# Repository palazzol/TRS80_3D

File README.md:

# TRS80_3D

## Stereo 3D graphics on a TRS-80 Model III

#### To be seen at [Tandy Assembly 2022](http://www.tandyassembly.com/)

## RAMBO board - 1 Meg "RAMDisk"

## Simulated Video - click to animate (YouTube link)

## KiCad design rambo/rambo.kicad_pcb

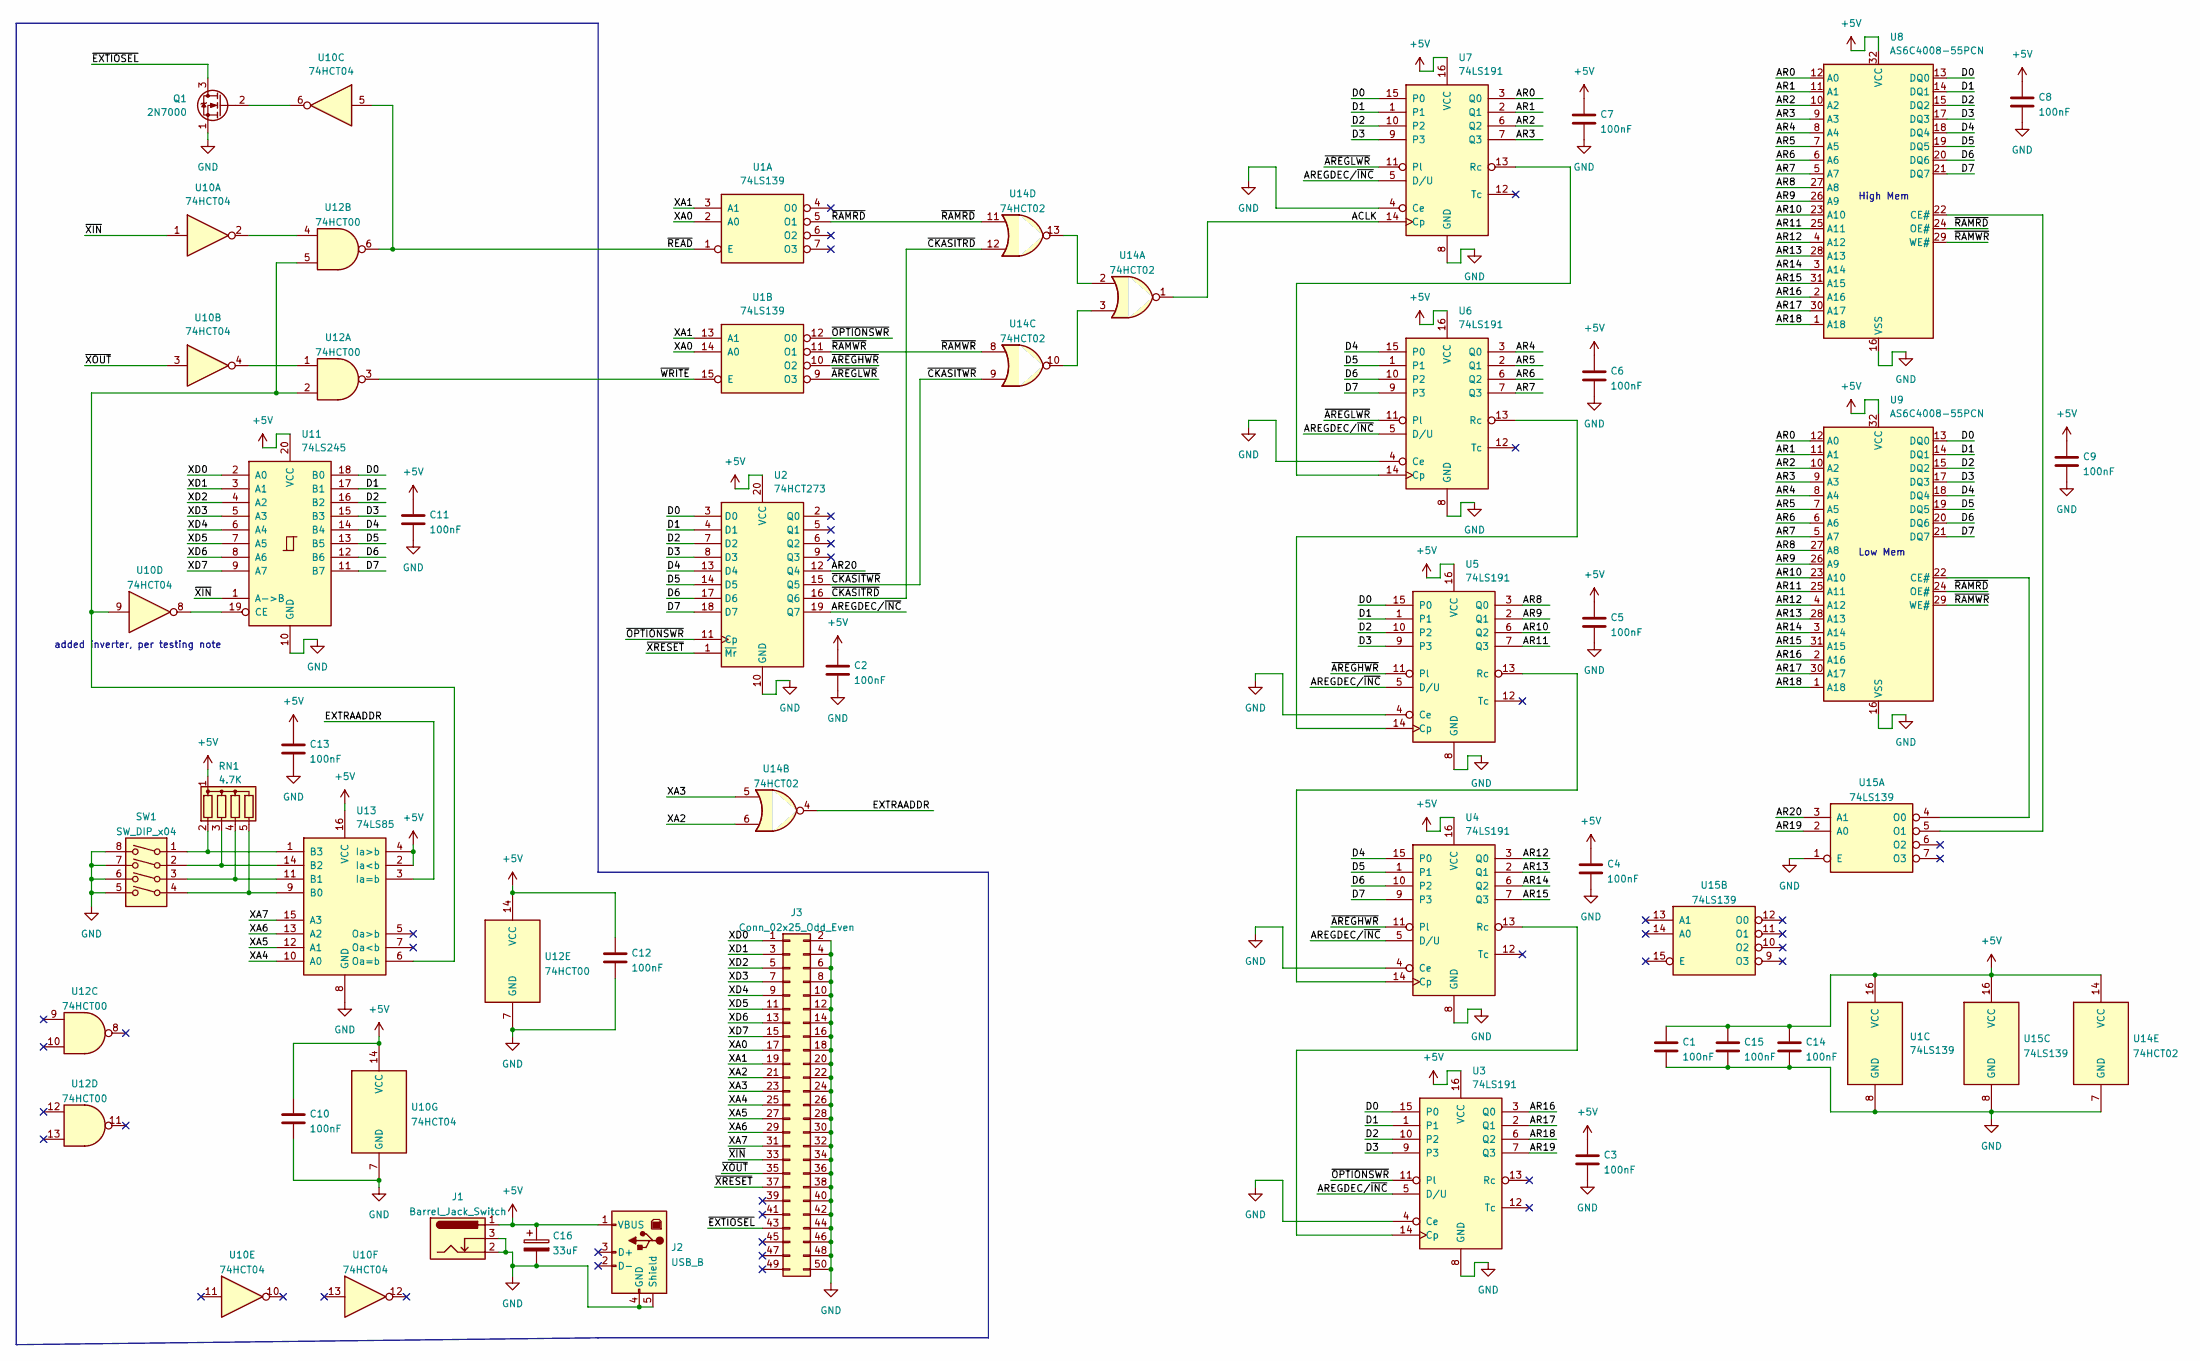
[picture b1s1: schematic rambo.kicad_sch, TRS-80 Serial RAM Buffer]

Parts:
C1, C2, C3, C4, C5, C6, C7, C8, C9, C10, C11, C12, C13, C14, C15: 100nF; C_Disc_D3.8mm_W2.6mm_P2.50mm
C16: 33uF; CP_Radial_D6.3mm_P2.50mm
J1: Barrel_Jack_Switch
J2: USB_B; USB_B_OST_USB-B1HSxx_Horizontal
J3: Conn_02x25_Odd_Even; PinHeader_2x25_P2.54mm_Vertical
Q1: 2N7000; TO-92_Inline
RN1: 4.7K; R_Array_SIP5
SW1: SW_DIP_x04; SW_DIP_SPSTx04_Slide_9.78x12.34mm_W7.62mm_P2.54mm
U1, U15: 74LS139; DIP-16_W7.62mm
U2: 74HCT273; DIP-20_W7.62mm
U3, U4, U5, U6, U7: 74LS191; DIP-16_W7.62mm
U8, U9: AS6C4008-55PCN; DIP-32_W15.24mm
U10: 74HCT04; DIP-14_W7.62mm
U11: 74LS245; DIP-20_W7.62mm
U12: 74HCT00; DIP-14_W7.62mm
U13: 74LS85; DIP-16_W7.62mm
U14: 74HCT02; DIP-14_W7.62mm

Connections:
+5V: C1.1, C2.1, C3.1, C4.1, C5.1, C6.1, C7.1, C8.1, C9.1, C10.1, C11.1, C12.1, C13.1, C14.1, C15.1, C16.1, J1.1, J2.1 (VBUS), RN1.1 (common), U1.16 (VCC), U2.20 (VCC), U3.16 (VCC), U4.16 (VCC), U5.16 (VCC), U6.16 (VCC), U7.16 (VCC), U8.32 (VCC), U9.32 (VCC), U10.14 (VCC), U11.20 (VCC), U12.14 (VCC), U13.2 (Ia<b), U13.4 (Ia>b), U13.16 (VCC), U14.14 (VCC), U15.16 (VCC)
/ACLK: U7.14 (Cp), U14.1
/AR0: U7.3 (Q0), U8.12 (A0), U9.12 (A0)
/AR1: U7.2 (Q1), U8.11 (A1), U9.11 (A1)
/AR2: U7.6 (Q2), U8.10 (A2), U9.10 (A2)
/AR3: U7.7 (Q3), U8.9 (A3), U9.9 (A3)
/AR4: U6.3 (Q0), U8.8 (A4), U9.8 (A4)
/AR5: U6.2 (Q1), U8.7 (A5), U9.7 (A5)
/AR6: U6.6 (Q2), U8.6 (A6), U9.6 (A6)
/AR7: U6.7 (Q3), U8.5 (A7), U9.5 (A7)
/AR8: U5.3 (Q0), U8.27 (A8), U9.27 (A8)
/AR9: U5.2 (Q1), U8.26 (A9), U9.26 (A9)
/AR10: U5.6 (Q2), U8.23 (A10), U9.23 (A10)
/AR11: U5.7 (Q3), U8.25 (A11), U9.25 (A11)
/AR12: U4.3 (Q0), U8.4 (A12), U9.4 (A12)
/AR13: U4.2 (Q1), U8.28 (A13), U9.28 (A13)
/AR14: U4.6 (Q2), U8.3 (A14), U9.3 (A14)
/AR15: U4.7 (Q3), U8.31 (A15), U9.31 (A15)
/AR16: U3.3 (Q0), U8.2 (A16), U9.2 (A16)
/AR17: U3.2 (Q1), U8.30 (A17), U9.30 (A17)
/AR18: U3.6 (Q2), U8.1 (A18), U9.1 (A18)
/AR19: U3.7 (Q3), U15.2 (A0)
/AR20: U2.12 (Q4), U15.3 (A1)
/AREGDEC/~INC: U2.19 (Q7), U3.5 (D/U), U4.5 (D/U), U5.5 (D/U), U6.5 (D/U), U7.5 (D/U)
/D0: U2.3 (D0), U3.15 (P0), U5.15 (P0), U7.15 (P0), U8.13 (DQ0), U9.13 (DQ0), U11.18 (B0)
/D1: U2.4 (D1), U3.1, U5.1, U7.1, U8.14 (DQ1), U9.14 (DQ1), U11.17 (B1)
/D2: U2.7 (D2), U3.10 (P2), U5.10 (P2), U7.10 (P2), U8.15 (DQ2), U9.15 (DQ2), U11.16 (B2)
/D3: U2.8 (D3), U3.9 (P3), U5.9 (P3), U7.9 (P3), U8.17 (DQ3), U9.17 (DQ3), U11.15 (B3)
/D4: U2.13 (D4), U4.15 (P0), U6.15 (P0), U8.18 (DQ4), U9.18 (DQ4), U11.14 (B4)
/D5: U2.14 (D5), U4.1, U6.1, U8.19 (DQ5), U9.19 (DQ5), U11.13 (B5)
/D6: U2.17 (D6), U4.10 (P2), U6.10 (P2), U8.20 (DQ6), U9.20 (DQ6), U11.12 (B6)
/D7: U2.18 (D7), U4.9 (P3), U6.9 (P3), U8.21 (DQ7), U9.21 (DQ7), U11.11 (B7)
/EXTRAADDR: U13.3 (Ia=b), U14.4
/XA0: J3.17, U1.2 (A0), U1.14 (A0)
/XA1: J3.19, U1.3 (A1), U1.13 (A1)
/XA2: J3.21, U14.6
/XA3: J3.23, U14.5
/XA4: J3.25, U13.10 (A0)
/XA5: J3.27, U13.12 (A1)
/XA6: J3.29, U13.13 (A2)
/XA7: J3.31, U13.15 (A3)
/XD0: J3.1, U11.2 (A0)
/XD1: J3.3, U11.3 (A1)
/XD2: J3.5, U11.4 (A2)
/XD3: J3.7, U11.5 (A3)
/XD4: J3.9, U11.6 (A4)
/XD5: J3.11, U11.7 (A5)
/XD6: J3.13, U11.8 (A6)
/XD7: J3.15, U11.9 (A7)
/~AREGHWR: U1.10 (O2), U4.11 (Pl), U5.11 (Pl)
/~AREGLWR: U1.9 (O3), U6.11 (Pl), U7.11 (Pl)
/~CKASITRD: U2.16 (Q6), U14.12
/~CKASITWR: U2.15 (Q5), U14.9
/~EXTIOSEL: J3.43, Q1.3 (D)
/~OPTIONSWR: U1.12 (O0), U2.11 (Cp), U3.11 (Pl)
/~RAMRD: U1.5 (O1), U8.24 (OE#), U9.24 (OE#), U14.11
/~RAMWR: U1.11 (O1), U8.29 (WE#), U9.29 (WE#), U14.8
/~READ: U1.1 (E), U10.5, U12.6
/~WRITE: U1.15 (E), U12.3
/~XIN: J3.33, U10.1, U11.1 (A->B)
/~XOUT: J3.35, U10.3
/~XRESET: J3.37, U2.1 (~Mr)
GND: C1.2, C2.2, C3.2, C4.2, C5.2, C6.2, C7.2, C8.2, C9.2, C10.2, C11.2, C12.2, C13.2, C14.2, C15.2, C16.2, J1.2, J1.3, J2.4 (GND), J2.5 (Shield), J3.2, J3.4, J3.6, J3.8, J3.10, J3.12, J3.14, J3.16, J3.18, J3.20, J3.22, J3.24, J3.26, J3.28, J3.30, J3.32, J3.34, J3.36, J3.38, J3.40, J3.42, J3.44, J3.46, J3.48, J3.50, Q1.1 (S), SW1.5, SW1.6, SW1.7, SW1.8, U1.8 (GND), U2.10 (GND), U3.4 (Ce), U3.8 (GND), U4.4 (Ce), U4.8 (GND), U5.4 (Ce), U5.8 (GND), U6.4 (Ce), U6.8 (GND), U7.4 (Ce), U7.8 (GND), U8.16 (VSS), U9.16 (VSS), U10.7 (GND), U11.10 (GND), U12.7 (GND), U13.8 (GND), U14.7 (GND), U15.1 (E), U15.8 (GND)
unnamed: Q1.2 (G), U10.6
unnamed: RN1.2 (R1), SW1.1, U13.1 (B3)
unnamed: RN1.3 (R2), SW1.2, U13.14 (B2)
unnamed: RN1.4 (R3), SW1.3, U13.11 (B1)
unnamed: RN1.5 (R4), SW1.4, U13.9 (B0)
unnamed: U3.14 (Cp), U4.13 (Rc)
unnamed: U4.14 (Cp), U5.13 (Rc)
unnamed: U5.14 (Cp), U6.13 (Rc)
unnamed: U6.14 (Cp), U7.13 (Rc)
unnamed: U10.2, U12.4
unnamed: U10.4, U12.1
unnamed: U10.8, U11.19 (CE)
unnamed: U10.9, U12.2, U12.5, U13.6 (Oa=b)
unnamed: U14.3, U14.10
unnamed: U14.2, U14.13
unnamed: U9.22 (CE#), U15.4 (O0)
unnamed: U8.22 (CE#), U15.5 (O1)

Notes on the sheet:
added inverter, per testing note
Low Mem
High Mem

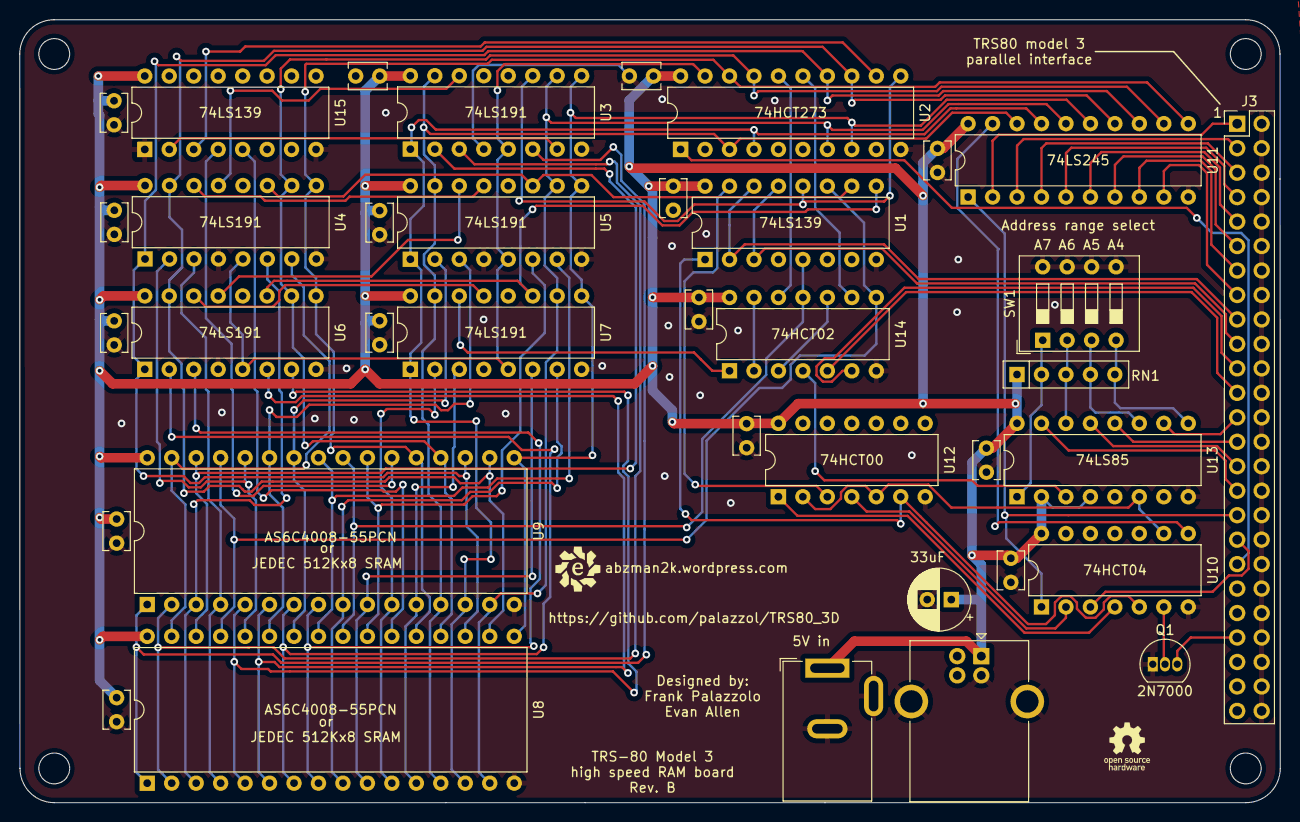
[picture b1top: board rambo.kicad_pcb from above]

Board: 2 copper layers, 130.9 x 81.3 mm, 41 parts (0 on the bottom side), 80 nets.

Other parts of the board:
h1, h2, h3, h4: MountingHole_3.2mm_M3

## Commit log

2022-08-08 WIP Ram Board
2022-08-08 Add KiCAD .gitignore for Ram Board
2022-08-08 Add card edge connector and power connector
    Still missing display LEDS, expansion connector
2022-08-09 Add TRS80 Display class
2022-08-09 Add RAM buffer schematic pdf (WIP)
2022-08-09 Update TRS80Display documentation
2022-08-09 Commit python code to create stereo image on screen, dump to a movie, or emit a frame to Z80 code
2022-08-09 Updates to build asm code generated by python
2022-08-09 footprints picked, capacitors added, beginning layout
2022-08-09 added usb b for power
2022-08-17 first layout done
2022-08-19 Modify code to support separate node list and line list
2022-08-19 fixed erc and drc
2022-08-20 added grbl
2022-08-22 Fix missing rocketship!
2022-08-22 Extract shape definitions from rendering script
2022-08-22 Tweak codecs for video output
2022-08-22 Allow for a border color, allow for out of bounds sets/resets
2022-08-22 Allow for variable number of frames when rendering, fix issue with perspective, remove unused back plane, update shapes
2022-09-18 Add Rambo Port Definitions and a Photo
2022-09-18 Fix for bottom right character not being part of freeze()
2022-09-28 Add updates for blit test. Add some docs.
2022-09-28 Remove old pillow version
2022-09-28 Add .gitignore
2022-09-29 inverted select fix
2022-09-29 added arduino code for the tester and modified EXR processor
2022-09-30 Stereo movie code! (Just in time)
2022-10-04 Updates from Tandy assembly.
    Build movies with 3d80.py -c3 and build.py
    Update port bits doc file with VBLANK mod details
